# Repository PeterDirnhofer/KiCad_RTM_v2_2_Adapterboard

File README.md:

# KiCad_RTM_v2_2_Adapterboard
## Bestellung Fischer 202301
500 EURO RTM KiCad Adapterboard

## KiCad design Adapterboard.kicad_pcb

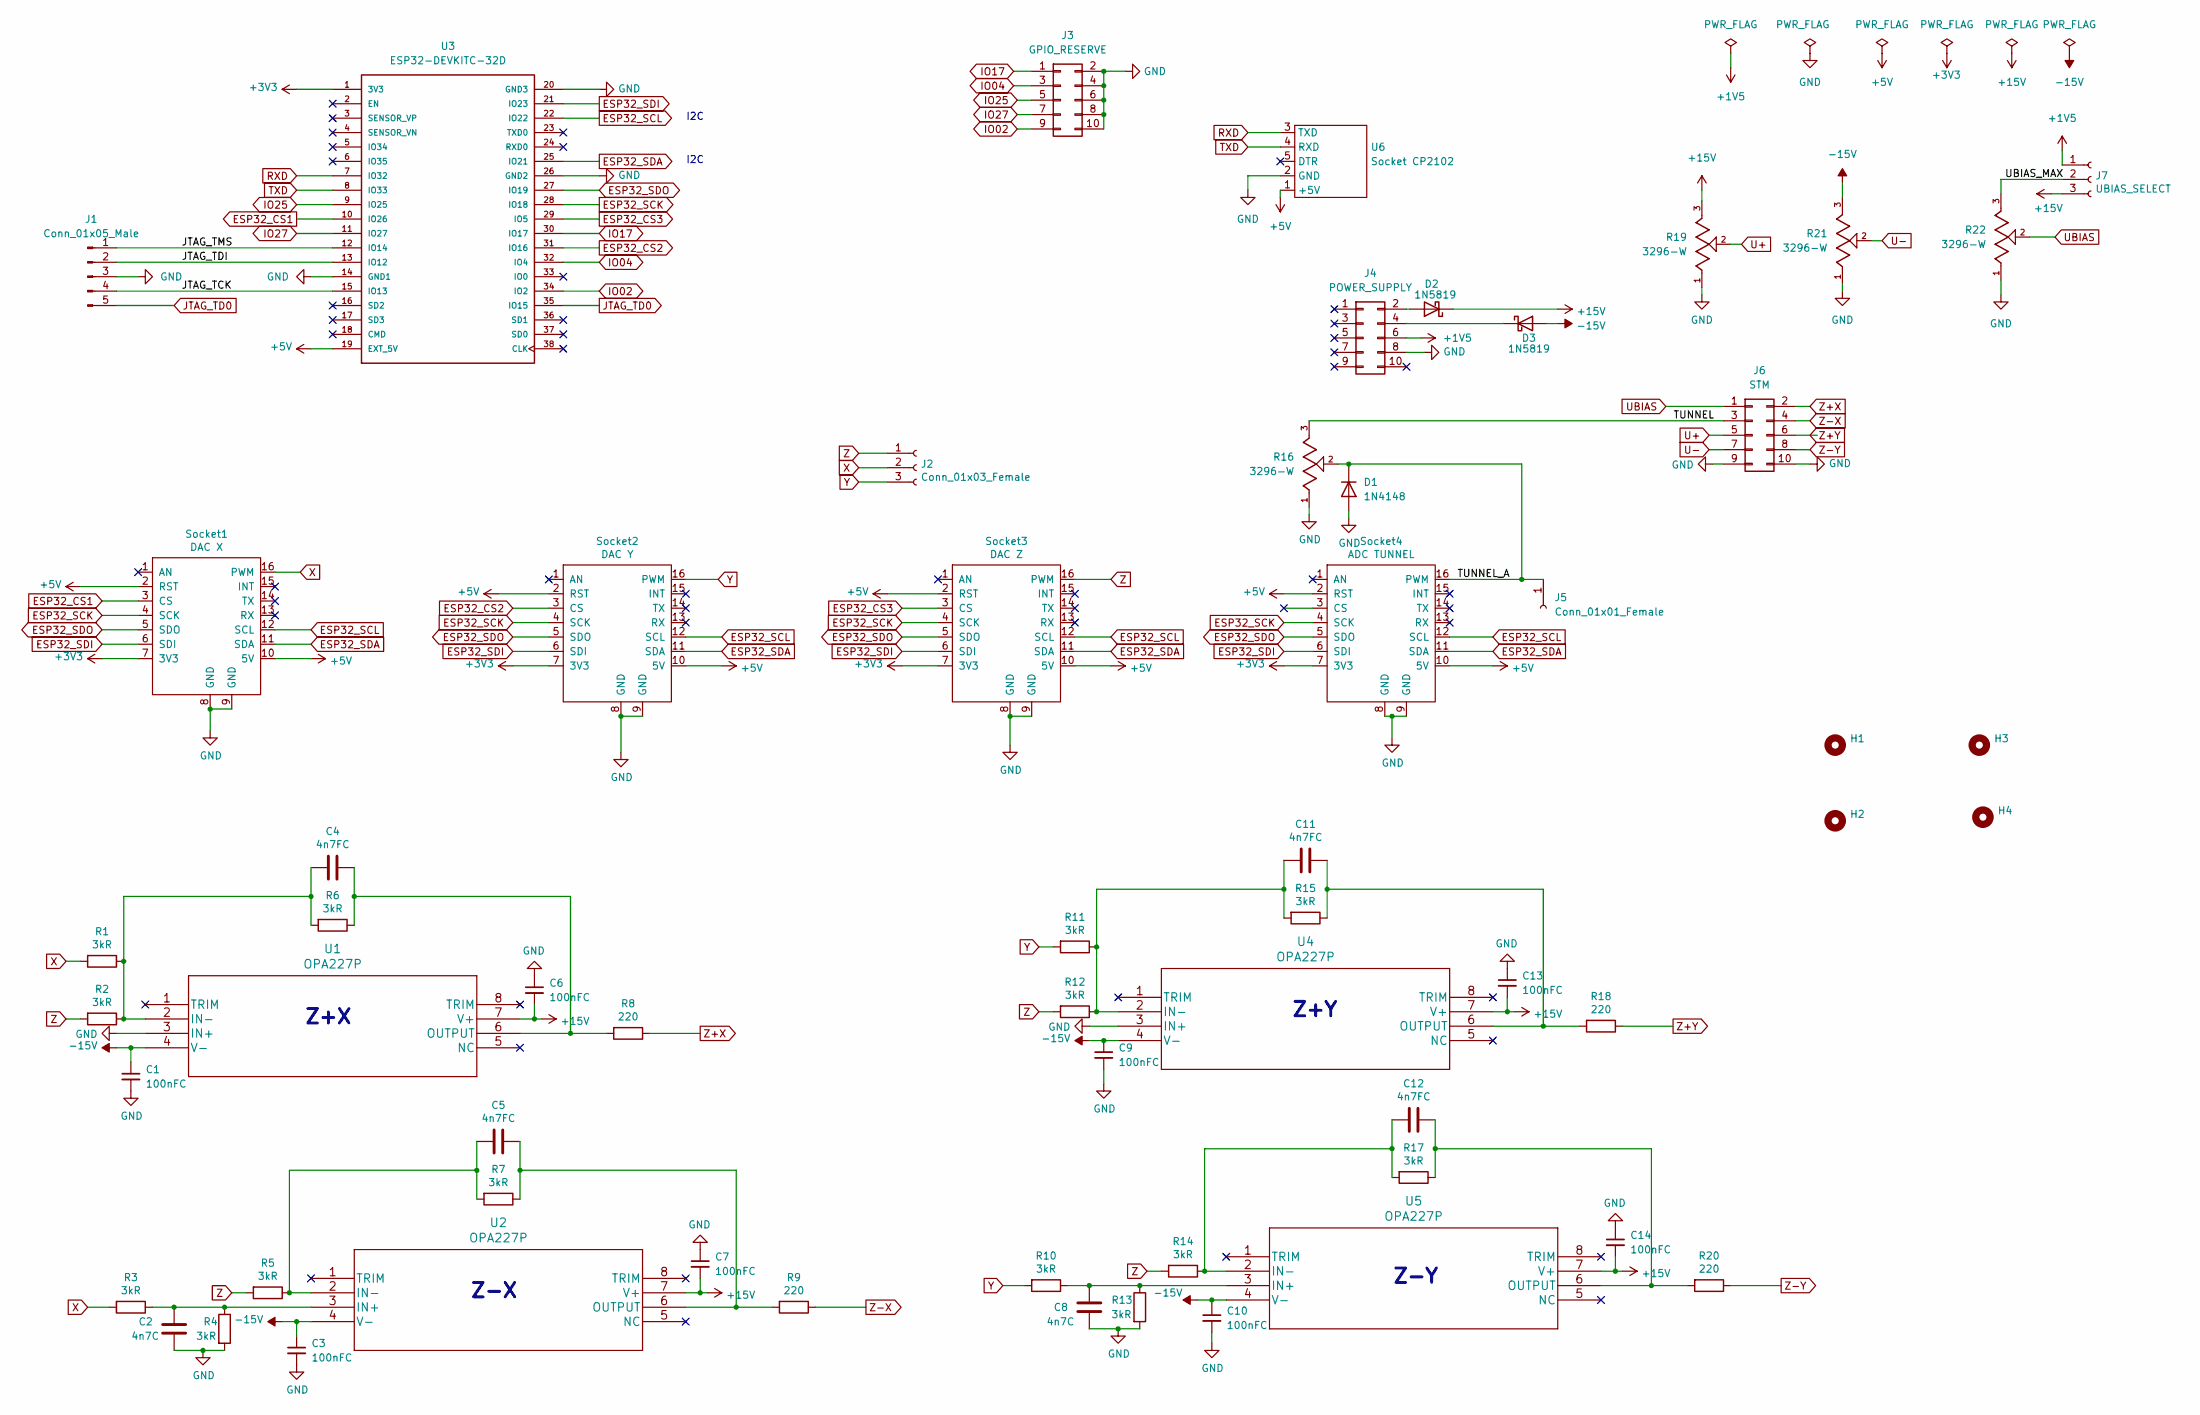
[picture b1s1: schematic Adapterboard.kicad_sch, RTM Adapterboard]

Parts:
C1, C3, C6, C7, C9, C10, C13, C14: 100nFC; C_Disc_D5.0mm_W2.5mm_P2.50mm
C2, C8: 4n7C; C_Disc_D5.0mm_W2.5mm_P2.50mm
C4, C5, C11, C12: 4n7FC; C_Disc_D5.0mm_W2.5mm_P2.50mm
D1: 1N4148; D_DO-35_SOD27_P7.62mm_Horizontal
D2, D3: 1N5819; D_DO-41_SOD81_P10.16mm_Horizontal
H1, H2, H3, H4: MountingHole_3.2mm_M3
J1: Conn_01x05_Male; PinHeader_1x05_P2.54mm_Vertical
J2: Conn_01x03_Female; PinSocket_1x03_P2.54mm_Vertical
J3: GPIO_RESERVE; PinHeader_2x05_P2.54mm_Vertical
J4: POWER_SUPPLY; PinHeader_2x05_P2.54mm_Vertical
J5: Conn_01x01_Female; PinHeader_1x01_P2.54mm_Vertical
J6: STM; PinHeader_2x05_P2.54mm_Vertical
J7: UBIAS_SELECT; PinHeader_1x03_P2.54mm_Vertical
R1, R2, R3, R4, R5, R6, R7, R10, R11, R12, R13, R14, R15, R17: 3kR; R_Axial_DIN0207_L6.3mm_D2.5mm_P10.16mm_Horizontal
R8, R9, R18, R20: 220; R_Axial_DIN0207_L6.3mm_D2.5mm_P10.16mm_Horizontal
R16, R19, R21, R22: 3296-W; Potentiometer_Bourns_3296W_Vertical; PARTREV 08/19
Socket1: DAC X; Mikroe_Socket
Socket2: DAC Y; Mikroe_Socket
Socket3: DAC Z; Mikroe_Socket
Socket4: ADC TUNNEL; Mikroe_Socket
U1, U2, U4, U5: OPA227P; DIP-8_W7.62mm_LongPads
U3: ESP32-DEVKITC-32D; MODULE_ESP32-DEVKITC-32D; PARTREV 4
U6: Socket CP2102; CP2102_USB

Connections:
+1V5: J4.6, J7.1
+3V3: Socket1.7 (3V3), Socket2.7 (3V3), Socket3.7 (3V3), Socket4.7 (3V3), U3.1 (3V3)
+5V: Socket1.2 (RST), Socket1.10 (5V), Socket2.2 (RST), Socket2.10 (5V), Socket3.2 (RST), Socket3.10 (5V), Socket4.2 (RST), Socket4.10 (5V), U3.19 (EXT_5V), U6.1 (+5V)
+15V: C6.2, C7.2, C13.2, C14.2, D2.1 (K), J7.3, R19.3, U1.7 (V+), U2.7 (V+), U4.7 (V+), U5.7 (V+)
-15V: C1.1, C3.1, C9.1, C10.1, D3.2 (A), R21.3, U1.4 (V-), U2.4 (V-), U4.4 (V-), U5.4 (V-)
/JTAG_TCK: J1.4, U3.15 (IO13)
/JTAG_TDI: J1.2, U3.13 (IO12)
/JTAG_TMS: J1.1, U3.12 (IO14)
/TUNNEL: J6.3, R16.3
/TUNNEL_A: D1.1 (K), J5.1, R16.2, Socket4.16 (PWM)
/UBIAS_MAX: J7.2, R22.3
ESP32_CS1: Socket1.3 (CS), U3.10 (IO26)
ESP32_CS2: Socket2.3 (CS), U3.31 (IO16)
ESP32_CS3: Socket3.3 (CS), U3.29 (IO5)
ESP32_SCK: Socket1.4 (SCK), Socket2.4 (SCK), Socket3.4 (SCK), Socket4.4 (SCK), U3.28 (IO18)
ESP32_SCL: Socket1.12 (SCL), Socket2.12 (SCL), Socket3.12 (SCL), Socket4.12 (SCL), U3.22 (IO22)
ESP32_SDA: Socket1.11 (SDA), Socket2.11 (SDA), Socket3.11 (SDA), Socket4.11 (SDA), U3.25 (IO21)
ESP32_SDI: Socket1.6 (SDI), Socket2.6 (SDI), Socket3.6 (SDI), Socket4.6 (SDI), U3.21 (IO23)
ESP32_SDO: Socket1.5 (SDO), Socket2.5 (SDO), Socket3.5 (SDO), Socket4.5 (SDO), U3.27 (IO19)
GND: C1.2, C2.2, C3.2, C6.1, C7.1, C8.2, C9.2, C10.2, C13.1, C14.1, D1.2 (A), J1.3, J3.2, J3.4, J3.6, J3.8, J3.10, J4.8, J6.9, J6.10, R4.2, R13.2, R16.1, R19.1, R21.1, R22.1, Socket1.8 (GND), Socket1.9 (GND), Socket2.8 (GND), Socket2.9 (GND), Socket3.8 (GND), Socket3.9 (GND), Socket4.8 (GND), Socket4.9 (GND), U1.3 (IN+), U3.14 (GND1), U3.20 (GND3), U3.26 (GND2), U4.3 (IN+), U6.2 (GND)
IO02: J3.9, U3.34 (IO2)
IO04: J3.3, U3.32 (IO4)
IO17: J3.1, U3.30 (IO17)
IO25: J3.5, U3.9 (IO25)
IO27: J3.7, U3.11 (IO27)
JTAG_TD0: J1.5, U3.35 (IO15)
unnamed: C2.1, R3.1, R4.1, U2.3 (IN+)
unnamed: C4.1, R6.1, R8.2, U1.6 (OUTPUT)
unnamed: C4.2, R1.1, R2.1, R6.2, U1.2 (IN-)
unnamed: C5.1, R7.1, R9.2, U2.6 (OUTPUT)
unnamed: C5.2, R5.1, R7.2, U2.2 (IN-)
unnamed: C8.1, R10.1, R13.1, U5.3 (IN+)
unnamed: C11.1, R15.1, R18.2, U4.6 (OUTPUT)
unnamed: C11.2, R11.1, R12.1, R15.2, U4.2 (IN-)
unnamed: C12.1, R17.1, R20.2, U5.6 (OUTPUT)
unnamed: C12.2, R14.1, R17.2, U5.2 (IN-)
unnamed: D2.2 (A), J4.2
unnamed: D3.1 (K), J4.4
RXD: U3.7 (IO32), U6.3 (TXD)
TXD: U3.8 (IO33), U6.4 (RXD)
U+: J6.5, R19.2
U-: J6.7, R21.2
UBIAS: J6.1, R22.2
X: J2.2, R1.2, R3.2, Socket1.16 (PWM)
Y: J2.3, R10.2, R11.2, Socket2.16 (PWM)
Z: J2.1, R2.2, R5.2, R12.2, R14.2, Socket3.16 (PWM)
Z+X: J6.2, R8.1
Z+Y: J6.6, R18.1
Z-X: J6.4, R9.1
Z-Y: J6.8, R20.1

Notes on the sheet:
I2C
Z-Y
Z-X
Z+X
Z+Y

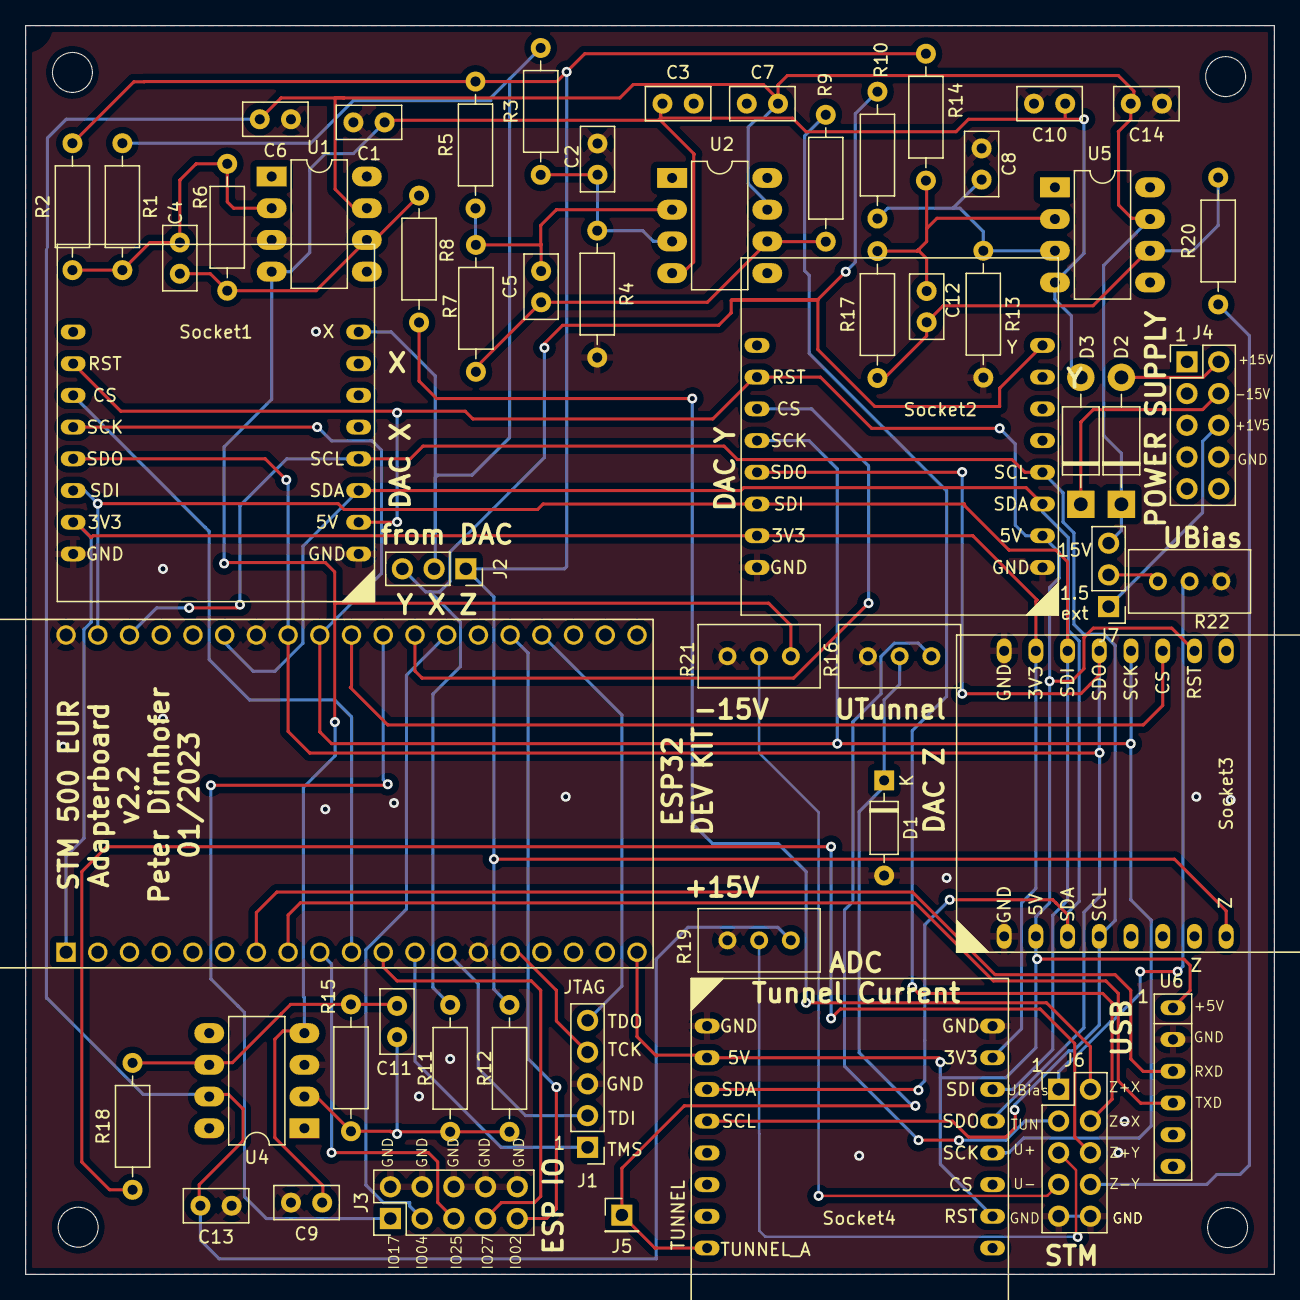
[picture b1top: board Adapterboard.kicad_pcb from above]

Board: 2 copper layers, 100.0 x 100.0 mm, 60 parts (0 on the bottom side), 50 nets.

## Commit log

2025-02-13 2nd commit
